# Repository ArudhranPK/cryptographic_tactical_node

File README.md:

# cryptographic_tactical_node
A Encryption based GPS tracker which send encrypted GPS coordinates to the Base Station and has tampering detection capabilities.

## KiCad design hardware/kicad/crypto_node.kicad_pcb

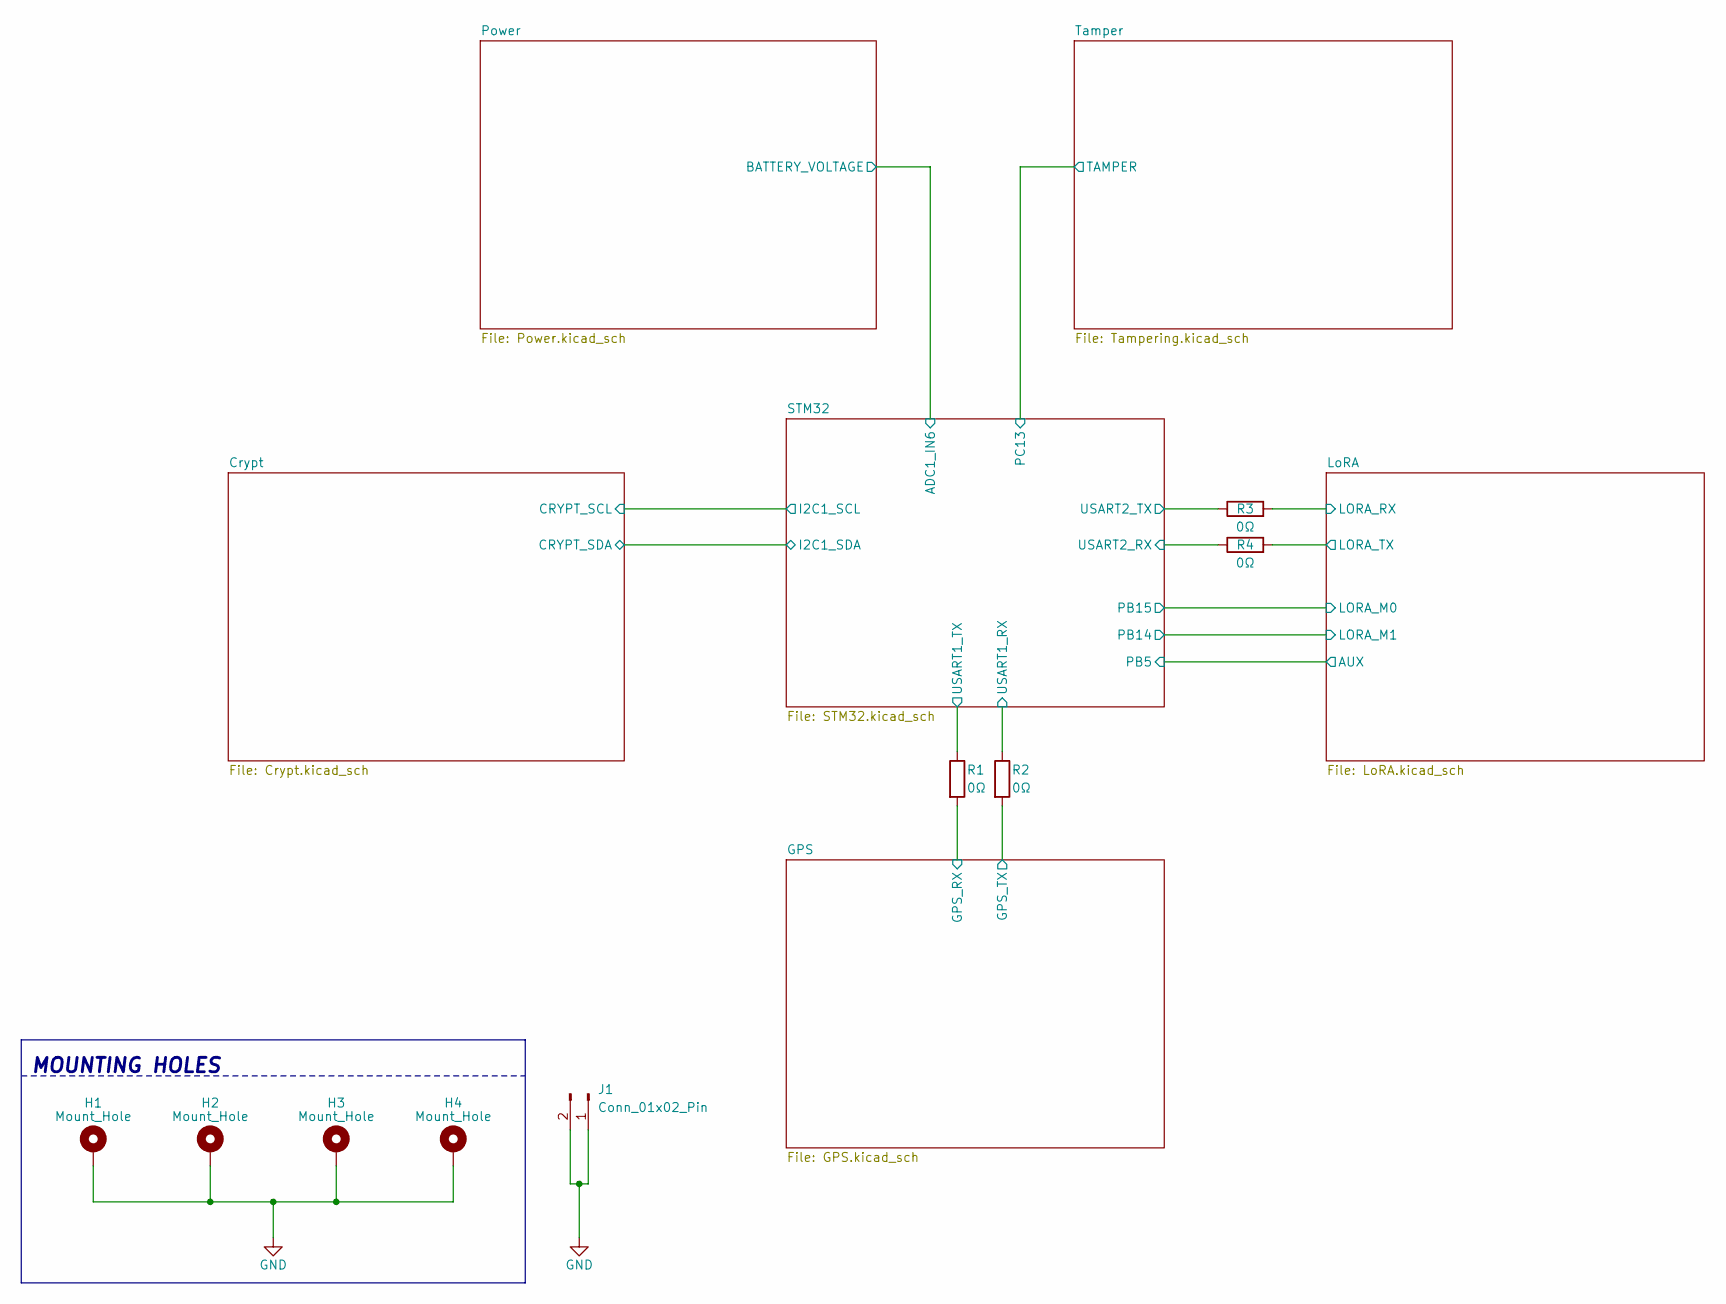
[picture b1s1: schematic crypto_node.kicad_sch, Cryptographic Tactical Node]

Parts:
H1, H2, H3, H4: Mount_Hole; MountingHole_3.2mm_M3_Pad_Via
J1: Conn_01x02_Pin; PinHeader_1x02_P2.54mm_Vertical
R1, R2, R3, R4: 0Ω; R_0805_2012Metric_Pad1.20x1.40mm_HandSolder

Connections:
/GPS/GPS_RX: R1.2; also elsewhere on the board
/GPS/GPS_TX: R2.2; also elsewhere on the board
/LoRA/LORA_RX: R3.2; also elsewhere on the board
/LoRA/LORA_TX: R4.2; also elsewhere on the board
/STM32/USART1_RX: R2.1; also elsewhere on the board
/STM32/USART1_TX: R1.1; also elsewhere on the board
/STM32/USART2_RX: R4.1; also elsewhere on the board
/STM32/USART2_TX: R3.1; also elsewhere on the board
GND: H1.1 (1_1), H2.1 (1_1), H3.1 (1_1), H4.1 (1_1), J1.1, J1.2; also elsewhere on the board

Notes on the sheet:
MOUNTING HOLES

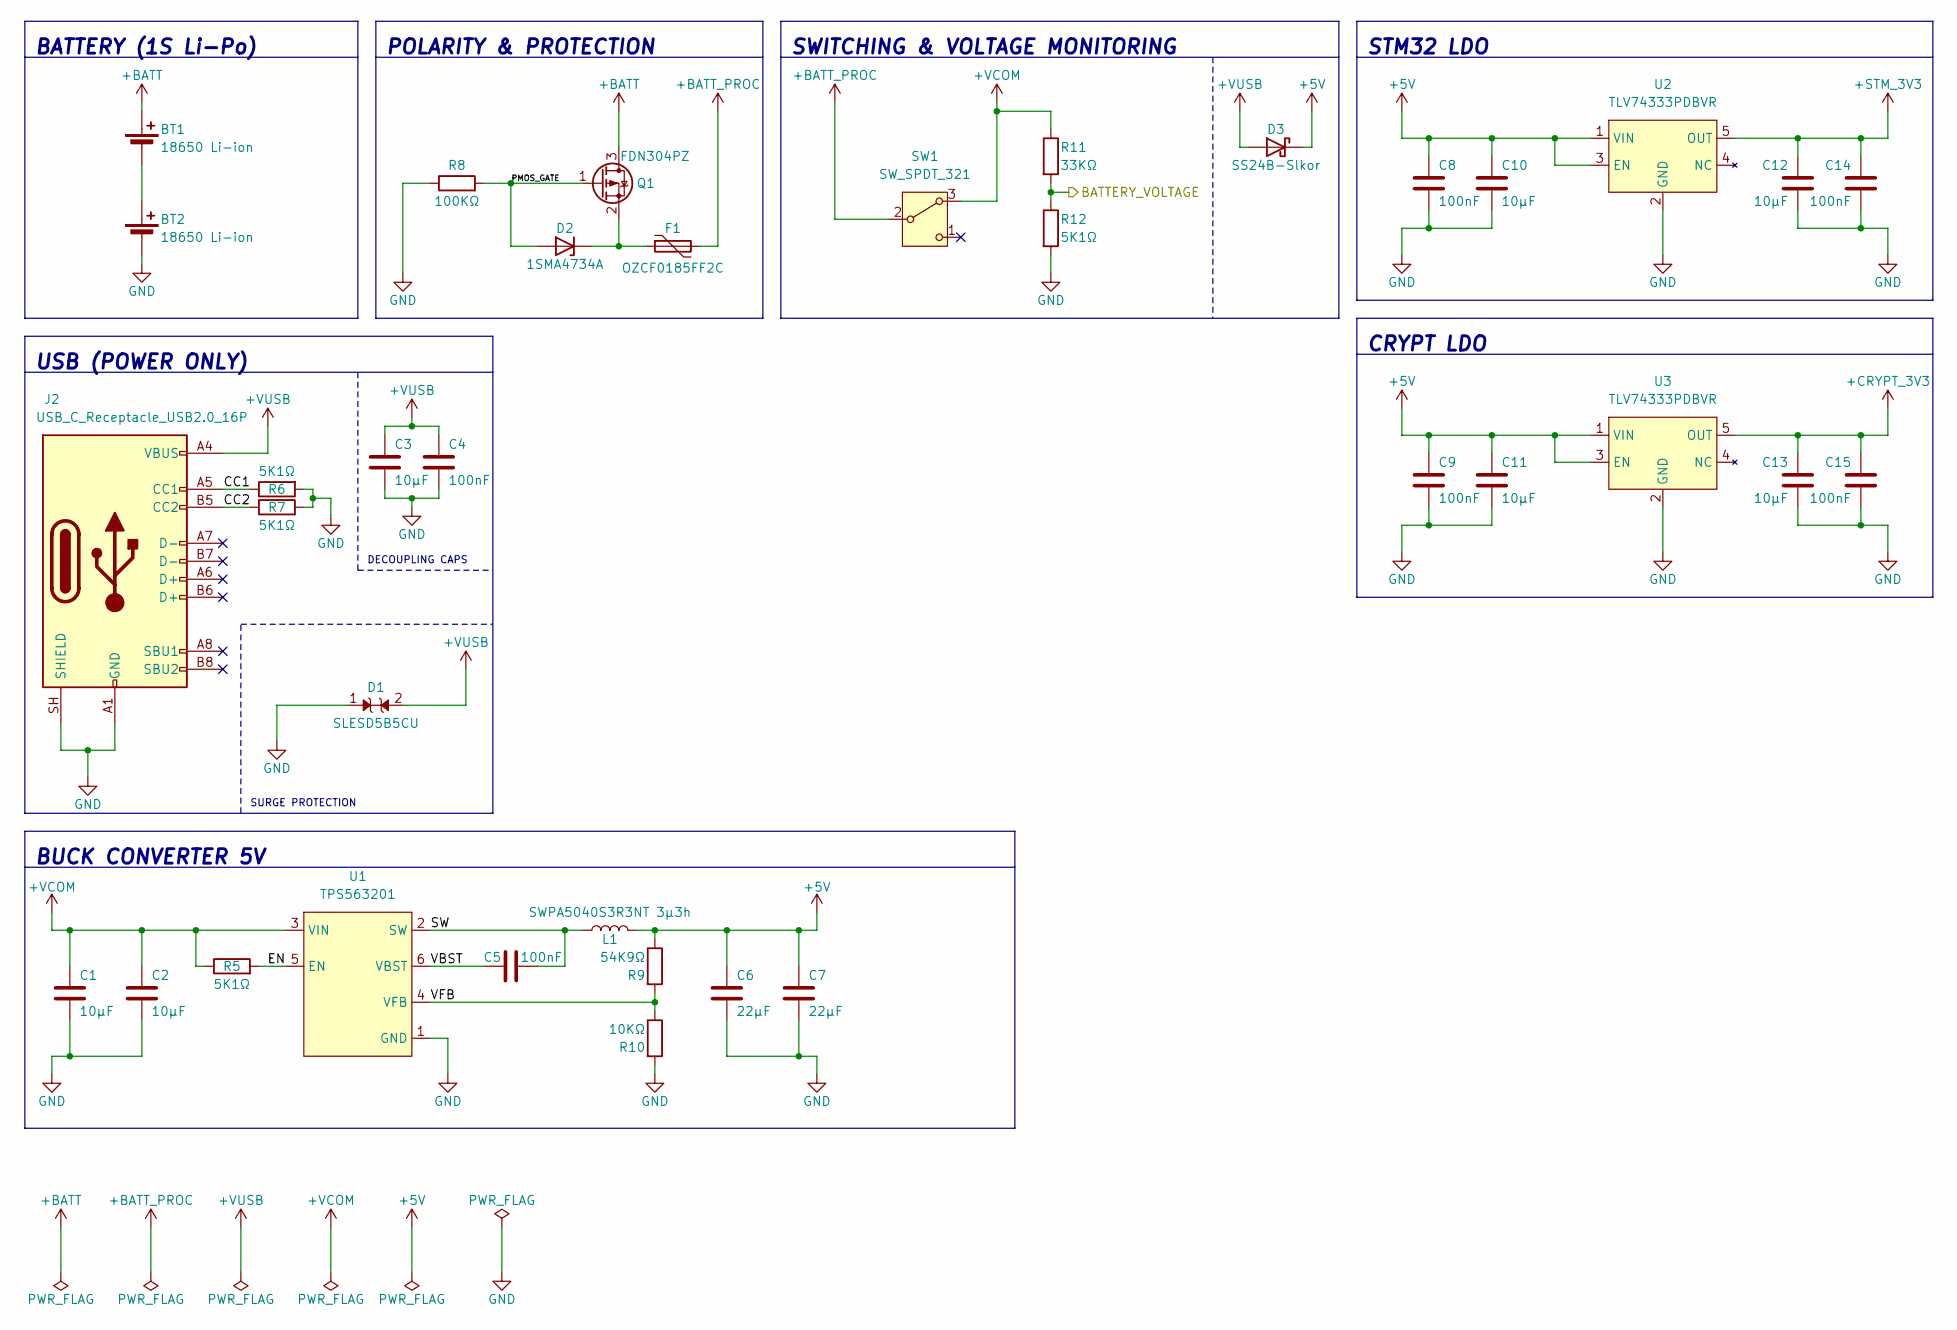
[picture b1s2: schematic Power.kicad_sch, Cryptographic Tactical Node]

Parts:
BT1, BT2: 18650 Li-ion; BatteryHolder_Keystone_1042_1x18650
C1, C2, C3, C10, C11, C12, C13: 10μF; C_1206_3216Metric_Pad1.33x1.80mm_HandSolder
C4, C5, C8, C9, C14, C15: 100nF; C_0603_1608Metric_Pad1.08x0.95mm_HandSolder
C6, C7: 22μF; C_1210_3225Metric_Pad1.33x2.70mm_HandSolder
D1: SLESD5B5CU; D_SOD-523
D2: 1SMA4734A; D_SMA
D3: SS24B-Slkor; D_SMA
F1: OZCF0185FF2C; Fuse_2920_7451Metric_Pad2.10x5.45mm_HandSolder
J2: USB_C_Receptacle_USB2.0_16P; USB_C_Receptacle_GCT_USB4105-xx-A_16P_TopMnt_Horizontal
L1: SWPA5040S3R3NT 3μ3h; L_Sunlord_SWPA5040S
Q1: FDN304PZ; SOT-23
R5, R6, R7, R12: 5K1Ω; R_0805_2012Metric_Pad1.20x1.40mm_HandSolder
R8: 100KΩ; R_0805_2012Metric_Pad1.20x1.40mm_HandSolder
R9: 54K9Ω; R_0805_2012Metric_Pad1.20x1.40mm_HandSolder
R10: 10KΩ; R_0805_2012Metric_Pad1.20x1.40mm_HandSolder
R11: 33KΩ; R_0805_2012Metric_Pad1.20x1.40mm_HandSolder
SW1: SW_SPDT_321; SS-12D10L7-XKB
U1: TPS563201; SOT-23-6
U2, U3: TLV74333PDBVR; SOT-23-5_HandSoldering

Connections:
+5V: C6.1, C7.1, C8.1, C9.1, C10.1, C11.1, D3.1 (K), L1.2, R9.1, U2.1 (VIN), U2.3 (EN), U3.1 (VIN), U3.3 (EN); also elsewhere on the board
+BATT: BT1.1 (+), Q1.3 (D)
+BATT_PROC: F1.2, SW1.2 (B)
+CRYPT_3V3: C13.1, C15.1, U3.5 (OUT); also elsewhere on the board
+STM_3V3: C12.1, C14.1, U2.5 (OUT); also elsewhere on the board
+VCOM: C1.1, C2.1, R5.1, R11.1, SW1.3 (A), U1.3 (VIN)
+VUSB: C3.1, C4.1, D1.2, D3.2 (A), J2.A4 (VBUS), J2.A9 (VBUS), J2.B4 (VBUS), J2.B9 (VBUS)
/Power/BATTERY_VOLTAGE: R11.2, R12.1; also elsewhere on the board
/Power/CC1: J2.A5 (CC1), R6.1
/Power/CC2: J2.B5 (CC2), R7.1
/Power/EN: R5.2, U1.5 (EN)
/Power/PMOS_GATE: D2.2 (A), Q1.1 (G), R8.2
/Power/SW: C5.2, L1.1, U1.2 (SW)
/Power/VBST: C5.1, U1.6 (VBST)
/Power/VFB: R9.2, R10.1, U1.4 (VFB)
GND: BT2.2 (-), C1.2, C2.2, C3.2, C4.2, C6.2, C7.2, C8.2, C9.2, C10.2, C11.2, C12.2, C13.2, C14.2, C15.2, D1.1, J2.A1 (GND), J2.A12 (GND), J2.B1 (GND), J2.B12 (GND), J2.SH (SHIELD), R6.2, R7.2, R8.1, R10.2, R12.2, U1.1 (GND), U2.2 (GND), U3.2 (GND); also elsewhere on the board
unnamed: BT1.2 (-), BT2.1 (+)
unnamed: D2.1 (K), F1.1, Q1.2 (S)

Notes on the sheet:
POLARITY & PROTECTION
BATTERY (1S Li-Po)
SWITCHING & VOLTAGE MONITORING
STM32 LDO
BUCK CONVERTER 5V
SURGE PROTECTION
DECOUPLING CAPS
USB (POWER ONLY)
CRYPT LDO

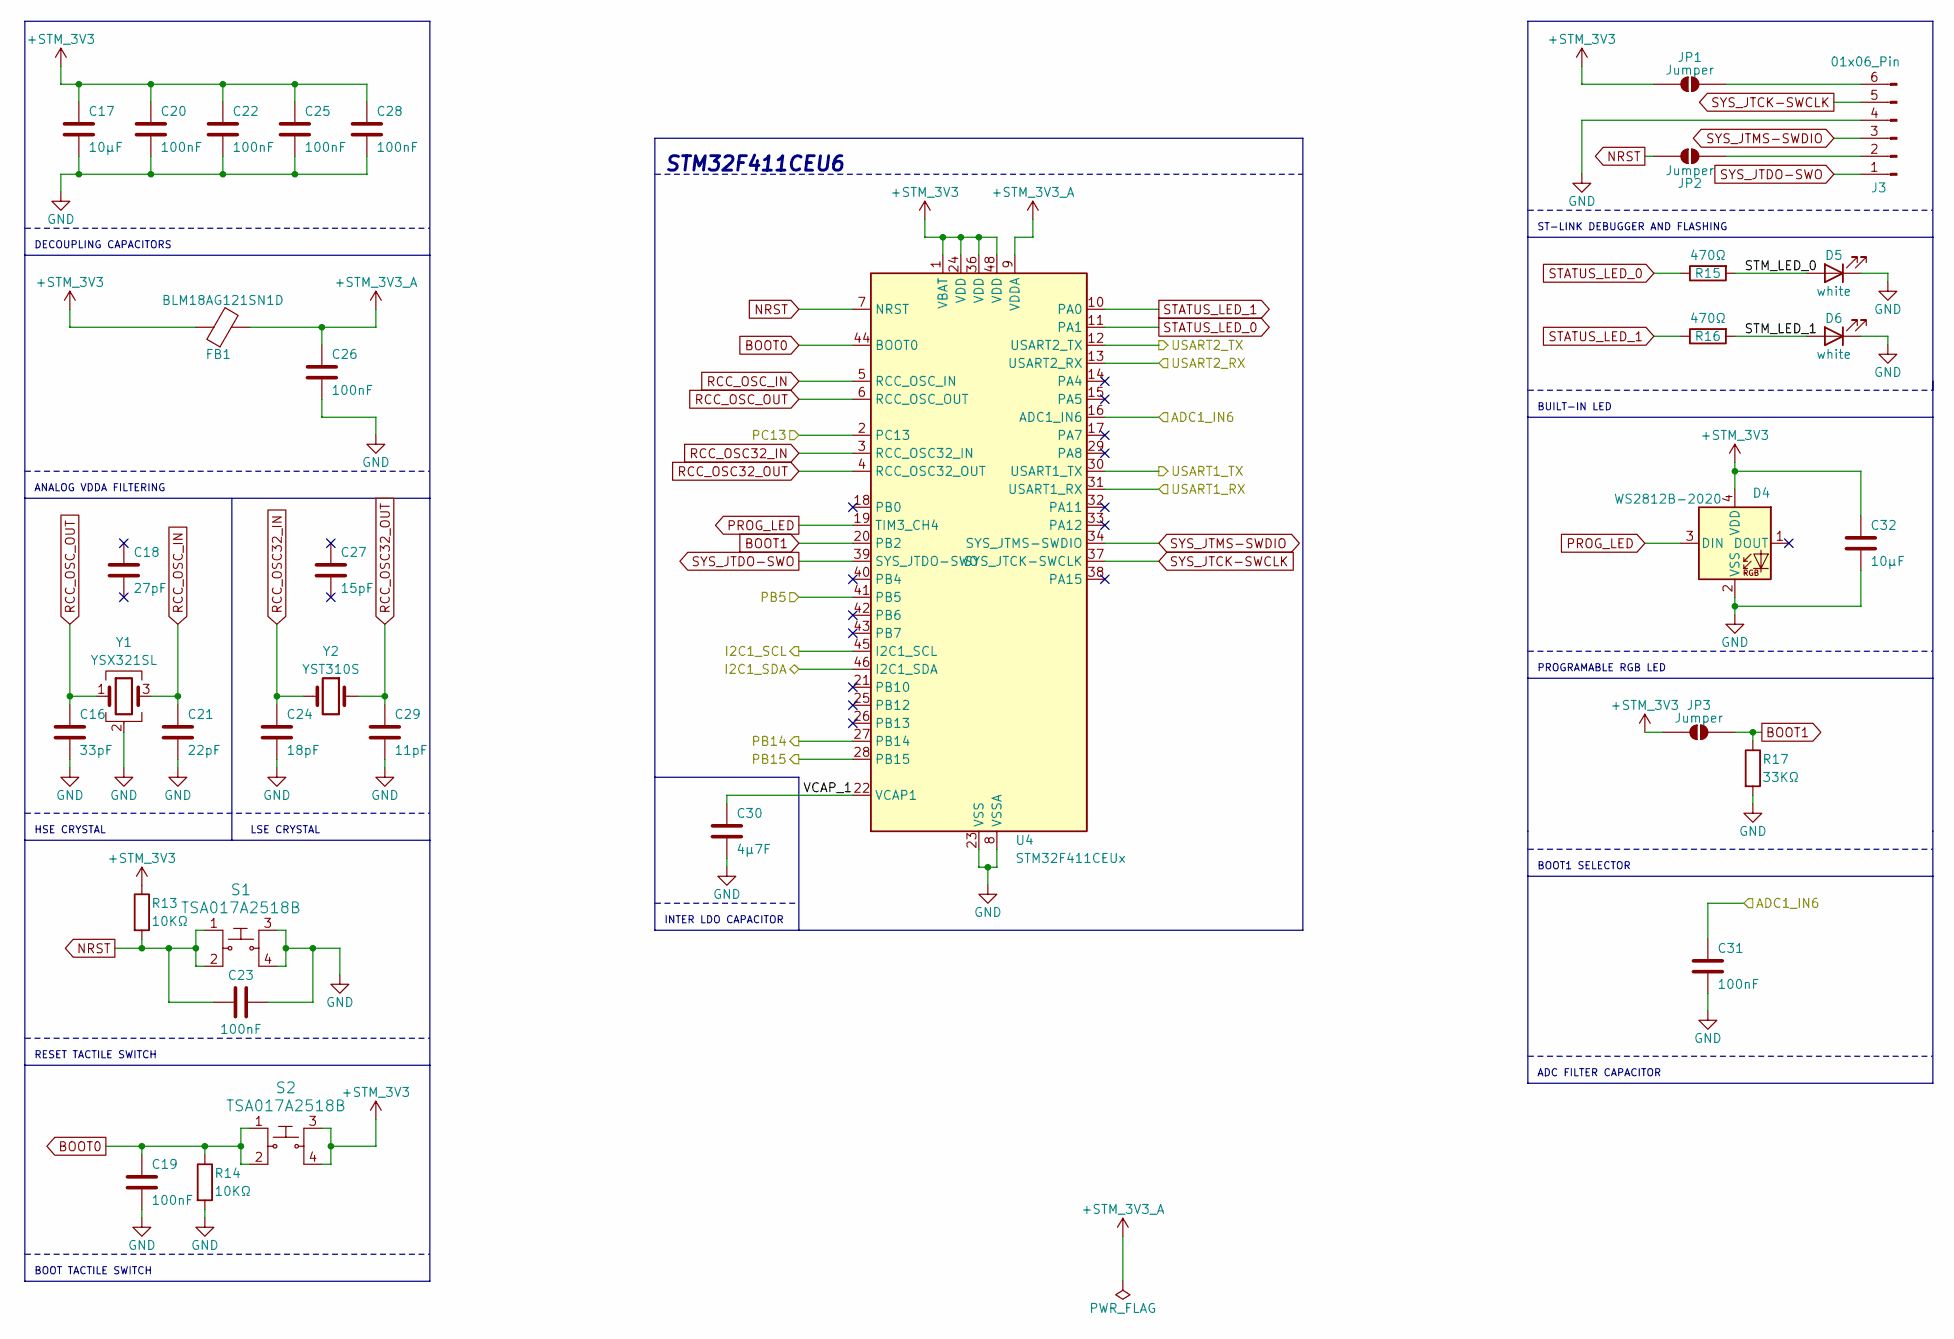
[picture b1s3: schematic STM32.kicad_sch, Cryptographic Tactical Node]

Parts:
C16: 33pF; C_0402_1005Metric_Pad0.74x0.62mm_HandSolder
C17, C32: 10μF; C_1206_3216Metric_Pad1.33x1.80mm_HandSolder
C18: 27pF; C_0402_1005Metric_Pad0.74x0.62mm_HandSolder
C19, C20, C22, C23, C25, C26, C28, C31: 100nF; C_0603_1608Metric_Pad1.08x0.95mm_HandSolder
C21: 22pF; C_0402_1005Metric_Pad0.74x0.62mm_HandSolder
C24: 18pF; C_0402_1005Metric_Pad0.74x0.62mm_HandSolder
C27: 15pF; C_0402_1005Metric_Pad0.74x0.62mm_HandSolder
C29: 11pF; C_0402_1005Metric_Pad0.74x0.62mm_HandSolder
C30: 4μ7F; C_0805_2012Metric_Pad1.18x1.45mm_HandSolder
D4: WS2812B-2020; LED_WS2812B-2020_PLCC4_2.0x2.0mm
D5, D6: white; LED_0805_2012Metric_Pad1.15x1.40mm_HandSolder
FB1: BLM18AG121SN1D; L_0805_2012Metric_Pad1.05x1.20mm_HandSolder
J3: 01x06_Pin; PinHeader_1x06_P2.54mm_Horizontal
JP1, JP2, JP3: Jumper; SolderJumper-2_P1.3mm_Open_RoundedPad1.0x1.5mm
R13, R14: 10KΩ; R_0805_2012Metric_Pad1.20x1.40mm_HandSolder
R15, R16: 470Ω; R_0805_2012Metric_Pad1.20x1.40mm_HandSolder
R17: 33KΩ; R_0805_2012Metric_Pad1.20x1.40mm_HandSolder
S1, S2: TSA017A2518B; MPN B3F-1000; Digi-Key_PN SW400-ND
U4: STM32F411CEUx; QFN-48-1EP_7x7mm_P0.5mm_EP5.6x5.6mm
Y1: YSX321SL; Crystal_SMD_3225-4Pin_3.2x2.5mm
Y2: YST310S; Crystal_SMD_3215-2Pin_3.2x1.5mm

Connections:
+STM_3V3: C17.1, C20.1, C22.1, C25.1, C28.1, C32.1, D4.4 (VDD), FB1.1, JP1.2 (B), JP3.2 (B), R13.1, S2.3, S2.4, U4.1 (VBAT), U4.24 (VDD), U4.36 (VDD), U4.48 (VDD); also elsewhere on the board
+STM_3V3_A: C26.1, FB1.2, U4.9 (VDDA)
/Crypt/CRYPT_SCL: U4.45 (I2C1_SCL); also elsewhere on the board
/Crypt/CRYPT_SDA: U4.46 (I2C1_SDA); also elsewhere on the board
/LoRA/AUX: U4.41 (PB5); also elsewhere on the board
/LoRA/LORA_M0: U4.28 (PB15); also elsewhere on the board
/LoRA/LORA_M1: U4.27 (PB14); also elsewhere on the board
/Power/BATTERY_VOLTAGE: C31.1, U4.16 (ADC1_IN6); also elsewhere on the board
/STM32/PC13: U4.2 (PC13); also elsewhere on the board
/STM32/STM_LED_0: D5.2 (A), R15.2
/STM32/STM_LED_1: D6.2 (A), R16.2
/STM32/USART1_RX: U4.31 (USART1_RX); also elsewhere on the board
/STM32/USART1_TX: U4.30 (USART1_TX); also elsewhere on the board
/STM32/USART2_RX: U4.13 (USART2_RX); also elsewhere on the board
/STM32/USART2_TX: U4.12 (USART2_TX); also elsewhere on the board
/STM32/VCAP_1: C30.1, U4.22 (VCAP1)
BOOT0: C19.1, R14.1, S2.1, S2.2, U4.44 (BOOT0)
BOOT1: JP3.1 (A), R17.1, U4.20 (PB2)
GND: C16.2, C17.2, C19.2, C20.2, C21.2, C22.2, C23.2, C24.2, C25.2, C26.2, C28.2, C29.2, C30.2, C31.2, C32.2, D4.2 (VSS), D5.1 (K), D6.1 (K), J3.4, R14.2, R17.2, S1.3, S1.4, U4.8 (VSSA), U4.23 (VSS), U4.35 (VSS), U4.47 (VSS), U4.49 (VSS), Y1.2 (G), Y1.4 (G); also elsewhere on the board
NRST: C23.1, JP2.2 (B), R13.2, S1.1, S1.2, U4.7 (NRST)
unnamed: J3.2, JP2.1 (A)
unnamed: J3.6, JP1.1 (A)
PROG_LED: D4.3 (DIN), U4.19 (TIM3_CH4)
RCC_OSC32_IN: C24.1, U4.3 (RCC_OSC32_IN), Y2.2
RCC_OSC32_OUT: C29.1, U4.4 (RCC_OSC32_OUT), Y2.1
RCC_OSC_IN: C21.1, U4.5 (RCC_OSC_IN), Y1.3
RCC_OSC_OUT: C16.1, U4.6 (RCC_OSC_OUT), Y1.1
STATUS_LED_0: R15.1, U4.11 (PA1)
STATUS_LED_1: R16.1, U4.10 (PA0)
SYS_JTCK-SWCLK: J3.5, U4.37 (SYS_JTCK-SWCLK)
SYS_JTDO-SWO: J3.1, U4.39 (SYS_JTDO-SWO)
SYS_JTMS-SWDIO: J3.3, U4.34 (SYS_JTMS-SWDIO)

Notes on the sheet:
STM32F411CEU6
PROGRAMABLE RGB LED
BUILT-IN LED
BOOT TACTILE SWITCH
DECOUPLING CAPACITORS
RESET TACTILE SWITCH
BOOT1 SELECTOR
INTER LDO CAPACITOR
HSE CRYSTAL
ST-LINK DEBUGGER AND FLASHING
LSE CRYSTAL
ADC FILTER CAPACITOR
ANALOG VDDA FILTERING

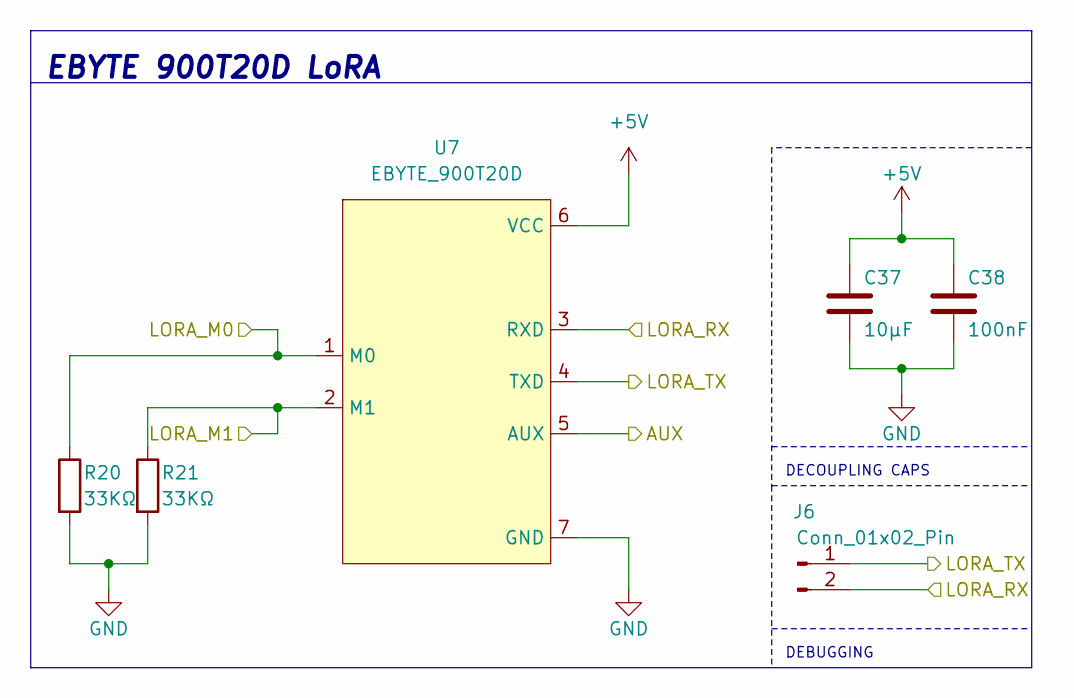
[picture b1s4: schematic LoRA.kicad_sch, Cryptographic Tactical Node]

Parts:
C37: 10μF; C_1206_3216Metric_Pad1.33x1.80mm_HandSolder
C38: 100nF; C_0603_1608Metric_Pad1.08x0.95mm_HandSolder
J6: Conn_01x02_Pin; PinHeader_1x02_P2.54mm_Vertical
R20, R21: 33KΩ; R_0805_2012Metric_Pad1.20x1.40mm_HandSolder
U7: EBYTE_900T20D

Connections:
+5V: C37.1, C38.1, U7.6 (VCC); also elsewhere on the board
/LoRA/AUX: U7.5 (AUX); also elsewhere on the board
/LoRA/LORA_M0: R20.1, U7.1 (M0); also elsewhere on the board
/LoRA/LORA_M1: R21.1, U7.2 (M1); also elsewhere on the board
/LoRA/LORA_RX: J6.2, U7.3 (RXD); also elsewhere on the board
/LoRA/LORA_TX: J6.1, U7.4 (TXD); also elsewhere on the board
GND: C37.2, C38.2, R20.2, R21.2, U7.7 (GND); also elsewhere on the board

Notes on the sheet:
EBYTE 900T20D LoRA
DECOUPLING CAPS
DEBUGGING

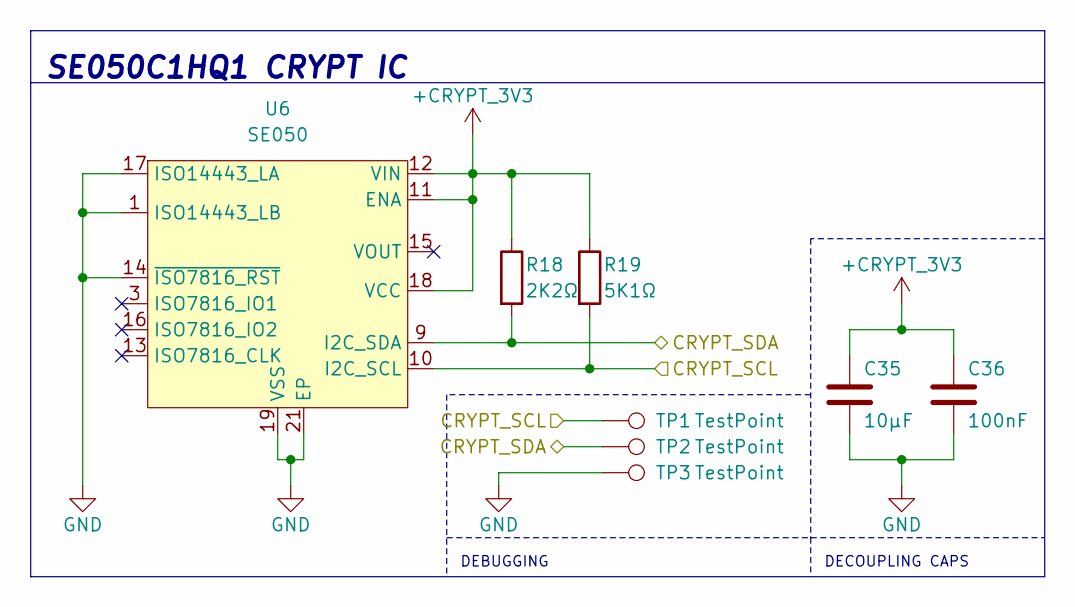
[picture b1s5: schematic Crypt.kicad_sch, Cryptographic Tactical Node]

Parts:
C35: 10μF; C_1206_3216Metric_Pad1.33x1.80mm_HandSolder
C36: 100nF; C_0603_1608Metric_Pad1.08x0.95mm_HandSolder
R18: 2K2Ω; R_0805_2012Metric_Pad1.20x1.40mm_HandSolder
R19: 5K1Ω; R_0805_2012Metric_Pad1.20x1.40mm_HandSolder
TP1, TP2, TP3: TestPoint; TestPoint_Pad_D1.5mm
U6: SE050; HX2QFN20

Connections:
+CRYPT_3V3: C35.1, C36.1, R18.1, R19.1, U6.11 (ENA), U6.12 (VIN), U6.18 (VCC); also elsewhere on the board
/Crypt/CRYPT_SCL: R19.2, TP1.1 (1_1), U6.10 (I2C_SCL); also elsewhere on the board
/Crypt/CRYPT_SDA: R18.2, TP2.1 (1_1), U6.9 (I2C_SDA); also elsewhere on the board
GND: C35.2, C36.2, TP3.1 (1_1), U6.1 (ISO14443_LB), U6.14 (~ISO7816_RST), U6.17 (ISO14443_LA), U6.19 (VSS), U6.21 (EP); also elsewhere on the board

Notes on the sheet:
DEBUGGING
SE050C1HQ1 CRYPT IC
DECOUPLING CAPS

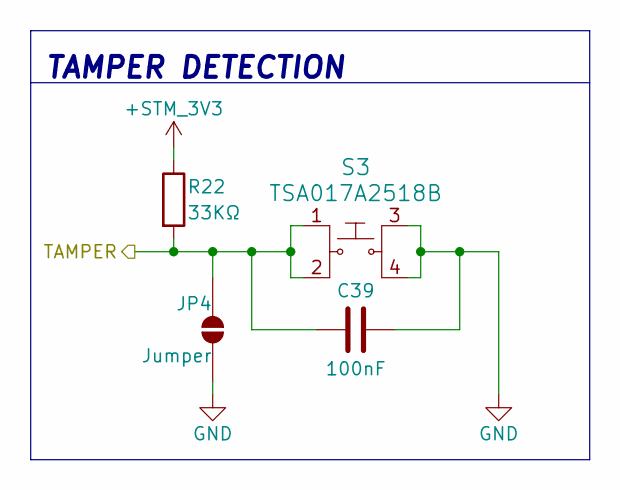
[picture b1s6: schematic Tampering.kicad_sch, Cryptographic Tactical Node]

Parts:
C39: 100nF; C_0603_1608Metric_Pad1.08x0.95mm_HandSolder
JP4: Jumper; SolderJumper-2_P1.3mm_Open_RoundedPad1.0x1.5mm
R22: 33KΩ; R_0805_2012Metric_Pad1.20x1.40mm_HandSolder
S3: TSA017A2518B; MPN B3F-1000; Digi-Key_PN SW400-ND

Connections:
+STM_3V3: R22.1; also elsewhere on the board
/STM32/PC13: C39.1, JP4.2 (B), R22.2, S3.1, S3.2; also elsewhere on the board
GND: C39.2, JP4.1 (A), S3.3, S3.4; also elsewhere on the board

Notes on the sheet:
TAMPER DETECTION

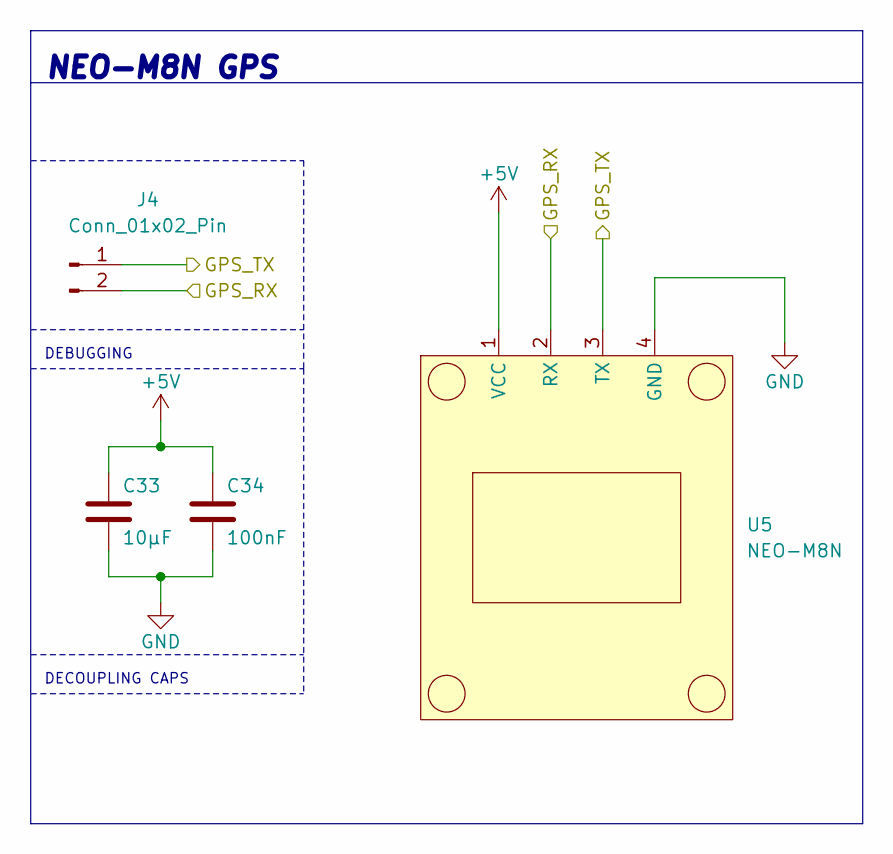
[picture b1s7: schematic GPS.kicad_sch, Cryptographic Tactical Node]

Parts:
C33: 10μF; C_1206_3216Metric_Pad1.33x1.80mm_HandSolder
C34: 100nF; C_0603_1608Metric_Pad1.08x0.95mm_HandSolder
J4: Conn_01x02_Pin; PinHeader_1x02_P2.54mm_Vertical
U5: NEO-M8N; NEO_M8N

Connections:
+5V: C33.1, C34.1, U5.1 (VCC); also elsewhere on the board
/GPS/GPS_RX: J4.2, U5.2 (RX); also elsewhere on the board
/GPS/GPS_TX: J4.1, U5.3 (TX); also elsewhere on the board
GND: C33.2, C34.2, U5.4 (GND); also elsewhere on the board

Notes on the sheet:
NEO-M8N GPS
DEBUGGING
DECOUPLING CAPS

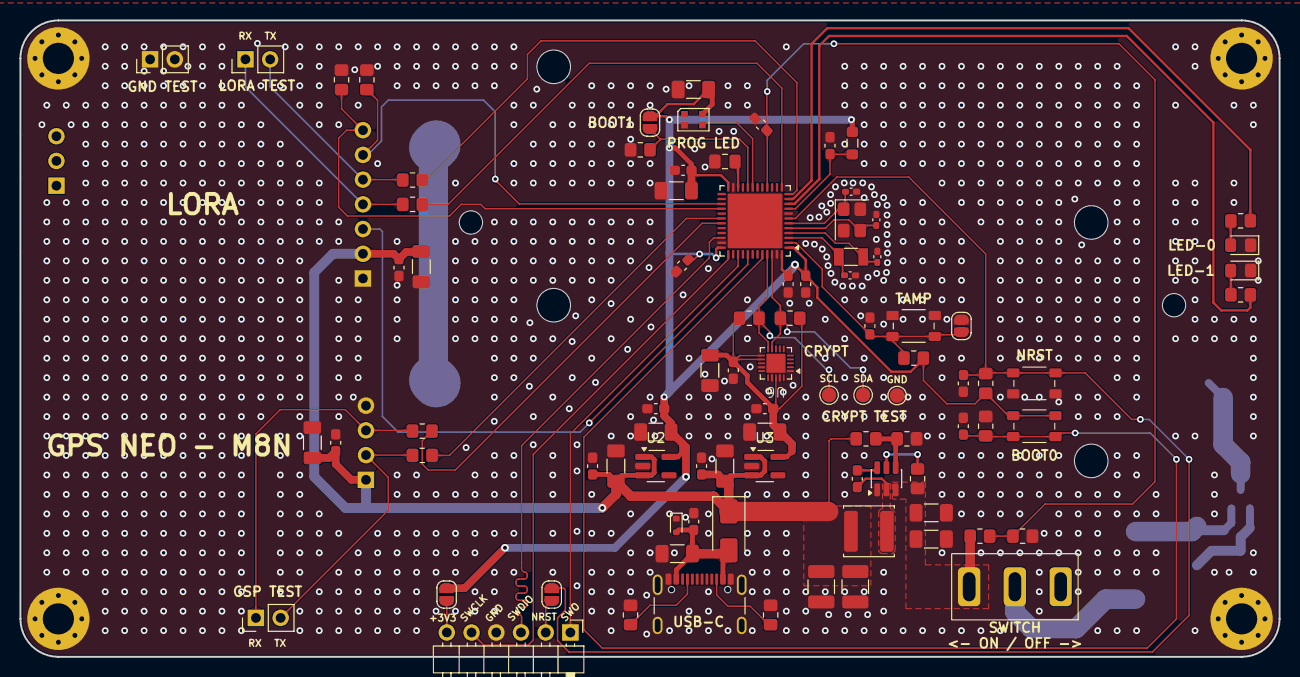
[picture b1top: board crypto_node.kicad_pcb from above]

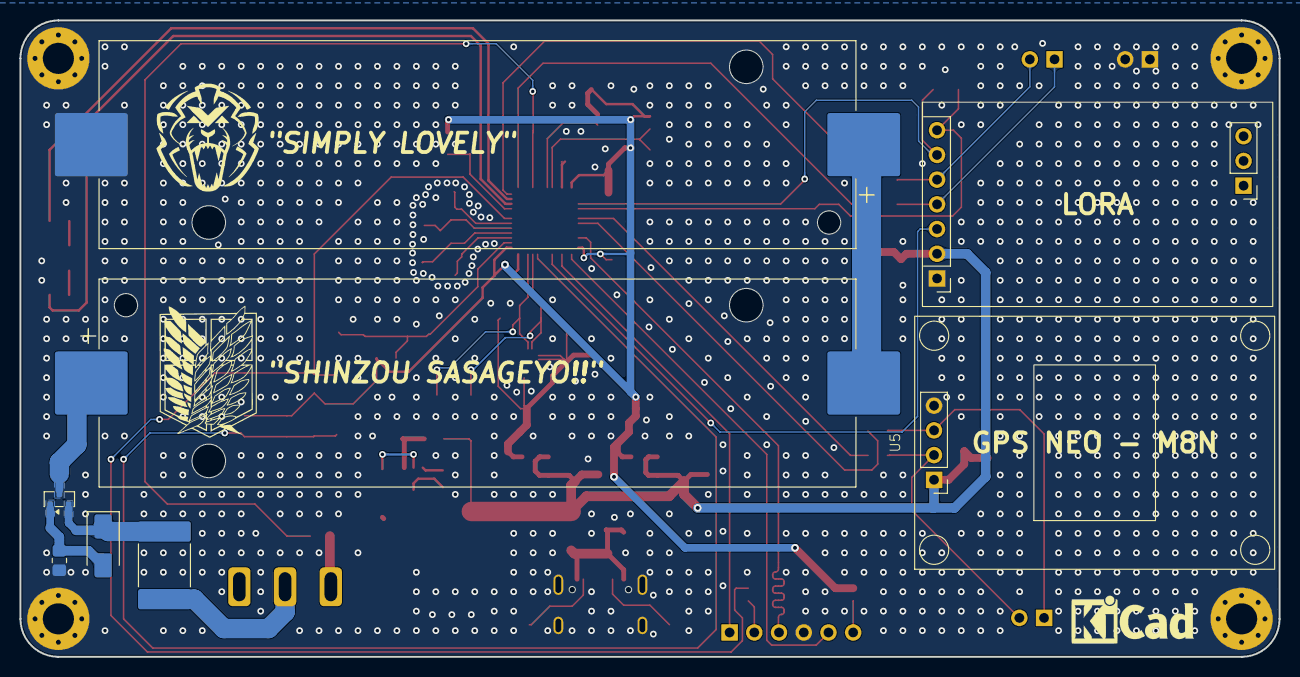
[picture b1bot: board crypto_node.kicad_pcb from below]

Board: 2 copper layers, 129.4 x 65.4 mm, 100 parts (8 on the bottom side), 51 nets.

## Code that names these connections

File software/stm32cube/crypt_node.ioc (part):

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Mcu.Name=STM32F411C(C-E)Ux
Mcu.Package=UFQFPN48
Mcu.UserName=STM32F411CEUx
PA10.Mode=Asynchronous
PA10.Signal=USART1_RX
PA13.Mode=Trace_Asynchronous_SW
PA13.Signal=SYS_JTMS-SWDIO
PA14.Mode=Trace_Asynchronous_SW
PA14.Signal=SYS_JTCK-SWCLK
PA2.Mode=Asynchronous
PA2.Signal=USART2_TX
PA3.Mode=Asynchronous
PA3.Signal=USART2_RX
PA6.Signal=ADCx_IN6
PA9.Mode=Asynchronous
PA9.Signal=USART1_TX
PB1.Signal=S_TIM3_CH4
PB12.GPIOParameters=GPIO_Label
PB12.GPIO_Label=STATUS_LED_0
PB12.Signal=GPIO_Output
PB13.GPIOParameters=GPIO_Label
PB13.GPIO_Label=STATUS_LED_1
PB13.Signal=GPIO_Output
PB14.GPIOParameters=GPIO_Label
PB14.GPIO_Label=LORA_M1
PB14.Signal=GPIO_Output
PB15.GPIOParameters=GPIO_Label
PB15.GPIO_Label=LORA_M0
PB15.Signal=GPIO_Output
PB3.Mode=Trace_Asynchronous_SW
PB3.Signal=SYS_JTDO-SWO
PB5.GPIOParameters=GPIO_Label
PB5.GPIO_Label=LORA_AUX
PB5.Signal=GPIO_Input
PB8.Mode=I2C
PB8.Signal=I2C1_SCL
PB9.Mode=I2C
PB9.Signal=I2C1_SDA
PC13-ANTI_TAMP.Signal=GPXTI13
PC14-OSC32_IN.Mode=LSE-External-Oscillator
PC14-OSC32_IN.Signal=RCC_OSC32_IN
PC15-OSC32_OUT.Mode=LSE-External-Oscillator
PC15-OSC32_OUT.Signal=RCC_OSC32_OUT
PH0\ -\ OSC_IN.Mode=HSE-External-Oscillator
PH0\ -\ OSC_IN.Signal=RCC_OSC_IN
PH1\ -\ OSC_OUT.Mode=HSE-External-Oscillator
PH1\ -\ OSC_OUT.Signal=RCC_OSC_OUT
RCC.HSE_VALUE=25000000
RCC.SYSCLKFreq_VALUE=16000000
board=custom

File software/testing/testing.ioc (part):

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Mcu.Name=STM32F411C(C-E)Ux
Mcu.Package=UFQFPN48
Mcu.UserName=STM32F411CEUx
PA0-WKUP.Signal=GPIO_Output
PA1.Signal=GPIO_Output
PA10.Mode=Asynchronous
PA10.Signal=USART1_RX
PA13.Mode=Trace_Asynchronous_SW
PA13.Signal=SYS_JTMS-SWDIO
PA14.Mode=Trace_Asynchronous_SW
PA14.Signal=SYS_JTCK-SWCLK
PA2.Mode=Asynchronous
PA2.Signal=USART2_TX
PA3.Mode=Asynchronous
PA3.Signal=USART2_RX
PA6.Signal=ADCx_IN6
PA9.Mode=Asynchronous
PA9.Signal=USART1_TX
PB1.GPIOParameters=GPIO_Speed
PB1.GPIO_Speed=GPIO_SPEED_FREQ_HIGH
PB1.Signal=S_TIM3_CH4
PB3.Mode=Trace_Asynchronous_SW
PB3.Signal=SYS_JTDO-SWO
PB8.Mode=I2C
PB8.Signal=I2C1_SCL
PB9.Mode=I2C
PB9.Signal=I2C1_SDA
PC14-OSC32_IN.Mode=LSE-External-Oscillator
PC14-OSC32_IN.Signal=RCC_OSC32_IN
PC15-OSC32_OUT.Mode=LSE-External-Oscillator
PC15-OSC32_OUT.Signal=RCC_OSC32_OUT
PH0\ -\ OSC_IN.Mode=HSE-External-Oscillator
PH0\ -\ OSC_IN.Signal=RCC_OSC_IN
PH1\ -\ OSC_OUT.Mode=HSE-External-Oscillator
PH1\ -\ OSC_OUT.Signal=RCC_OSC_OUT
RCC.HSE_VALUE=25000000
RCC.SYSCLKFreq_VALUE=100000000
RCC.SYSCLKSource=RCC_SYSCLKSOURCE_PLLCLK
board=custom
